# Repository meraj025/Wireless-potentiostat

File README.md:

# Wireless configurable potentiostat
Using Redbear Nano V2 and LMP91000 (TI) a wireless configurable and acquisition interface is designed, developed and tested.
Repository Contents
-------------------
* **/Libraries** - Arduino library and example sketches.
* **/PCB** - All Eagle design files (.brd, .sch)
* **/python** - All python files and GUI (.py, .ui)

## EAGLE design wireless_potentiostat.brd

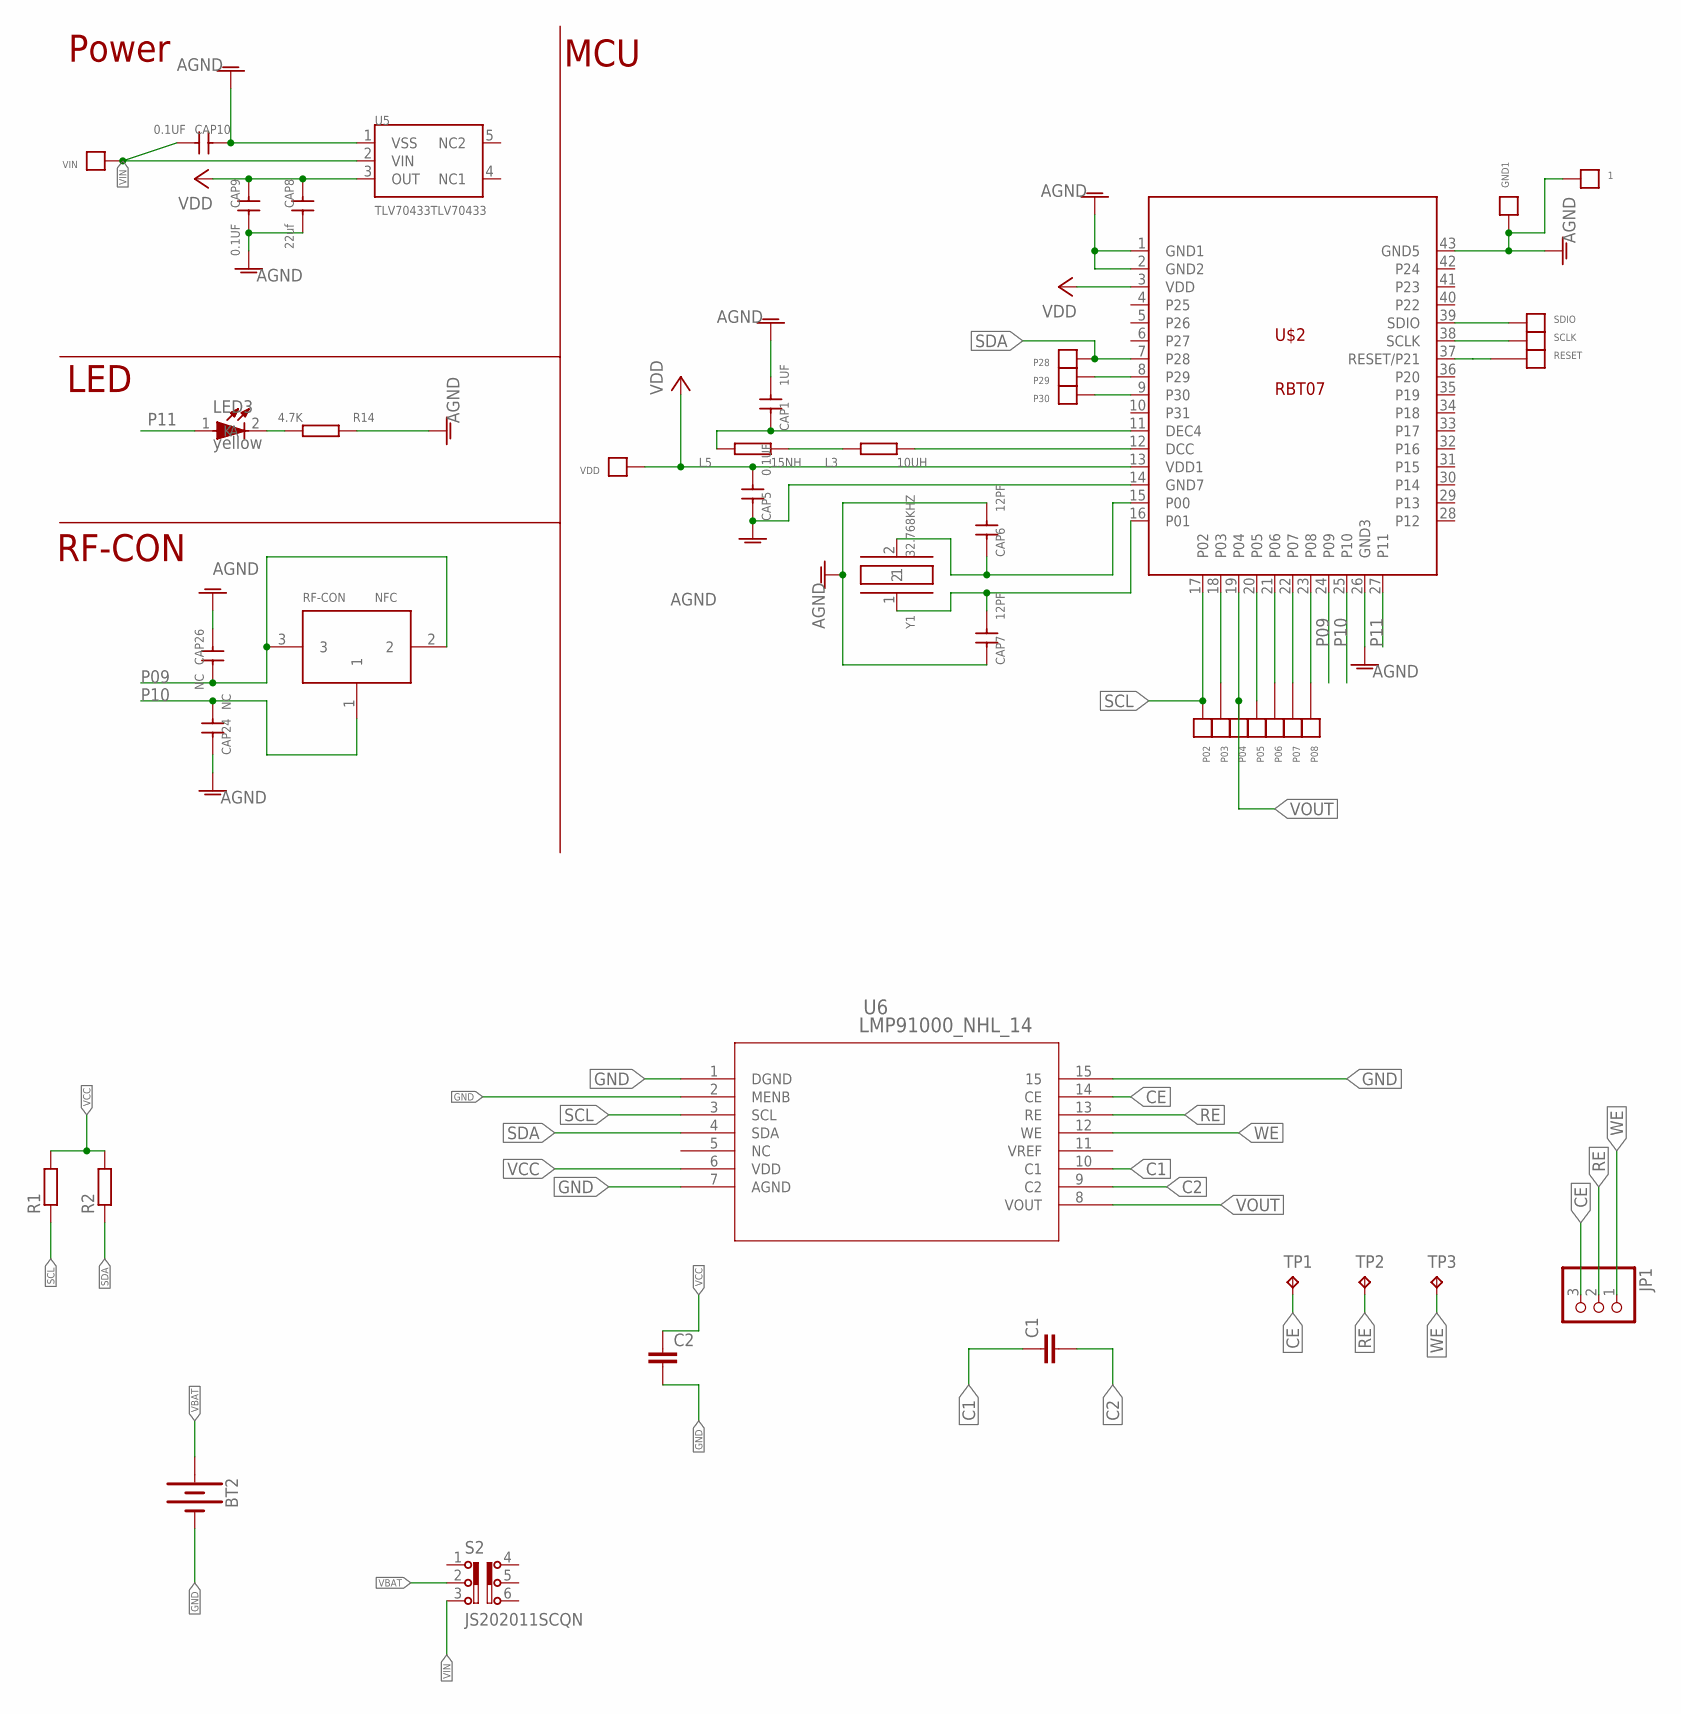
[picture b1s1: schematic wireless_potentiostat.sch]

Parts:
1: TPDOT_1; DOT_1
BT2: BATTERY-24.5MM_PTH; BATTCON_24.5MM_PTH
C1, C2: C-EUC0603; C0603
CAP1: 1UF; C-0402
CAP5, CAP9, CAP10: 0.1UF; C-0402
CAP6, CAP7: 12PF; C-0402
CAP8: 22uf; C0805
CAP24, CAP26: NC; C-0402
GND1: TPDOT_1.5; DOT_1.5
JP1: PINHD-1X3; 1X03
L3: 10UH; R0603
L5: 15NH; R0402
LED3: yellow; LED0603
P02, P04, P05, P29, P30: TPDOT_1.5; DOT_1.5
P03, P06, P07, P08: 1P
P28: TPTPEB; TPEB
R1, R2: R-EU_R0603; R0603
R14: 4.7K; R0402
RESET: 1P
RF-CON: NFC; IPEX
S2: JS202011SCQN
SCLK: TPDOT_1.5; DOT_1.5
SDIO: TPDOT_1.5; DOT_1.5
TP1, TP2, TP3: TPPAD1-13; P1-13
U5: TLV70433TLV70433; SOT-23-5
U6: LMP91000_NHL_14; SDA14B
U$2: RBT07
VDD: TPTPEB; TPEB
VIN: TPDOT_1; DOT_1
Y1: 32.768KHZ; CRY_3215

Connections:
C1: C1.1, U6.10 (C1)
C2: C1.2, U6.9 (C2)
CE: JP1.3, TP1.TP, U6.14 (CE)
GND: 1.1, BT2.2 (-), C2.2, CAP1.1, CAP5.2, CAP6.1, CAP7.2, CAP8.1, CAP9.1, CAP10.2, CAP24.2, CAP26.2, GND1.1, R14.1, U5.1 (VSS), U6.1 (DGND), U6.2 (MENB), U6.7 (AGND), U6.15, U$2.1 (GND1), U$2.2 (GND2), U$2.14 (GND7), U$2.26 (GND3), U$2.43 (GND5)
unnamed: L3.1, L5.2
unnamed: CAP1.2, L5.1, U$2.11 (DEC4)
unnamed: L3.2, U$2.12 (DCC)
unnamed: SDIO.1, U$2.39 (SDIO)
unnamed: SCLK.1, U$2.38 (SCLK)
unnamed: RESET.P$1, U$2.37 (RESET/P21)
unnamed: CAP7.1, U$2.16 (P01), Y1.1
unnamed: CAP6.2, U$2.15 (P00), Y1.2
unnamed: P03.P$1, U$2.18 (P03)
unnamed: P05.1, U$2.20 (P05)
unnamed: P06.P$1, U$2.21 (P06)
unnamed: P29.1, U$2.8 (P29)
unnamed: P07.P$1, U$2.22 (P07)
unnamed: P08.P$1, U$2.23 (P08)
unnamed: LED3.2 (K), R14.2
unnamed: P30.1, U$2.9 (P30)
P09: CAP26.1, RF-CON.2, RF-CON.3, U$2.24 (P09)
P10: CAP24.1, RF-CON.1, U$2.25 (P10)
P11: LED3.1 (A), U$2.27 (P11)
RE: JP1.2, TP2.TP, U6.13 (RE)
SCL: P02.1, R1.1, U6.3 (SCL), U$2.17 (P02)
SDA: P28.1, R2.1, U6.4 (SDA), U$2.7 (P28)
VBAT: BT2.3 (+), S2.2
VCC: C2.1, CAP5.1, CAP8.2, CAP9.2, R1.2, R2.2, U5.3 (OUT), U6.6 (VDD), U$2.3 (VDD), U$2.13 (VDD1), VDD.1
VIN: CAP10.1, S2.3, U5.2 (VIN), VIN.1
VOUT: P04.1, U6.8 (VOUT), U$2.19 (P04)
WE: JP1.1, TP3.TP, U6.12 (WE)

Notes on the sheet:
LED
RF-CON
Power
MCU

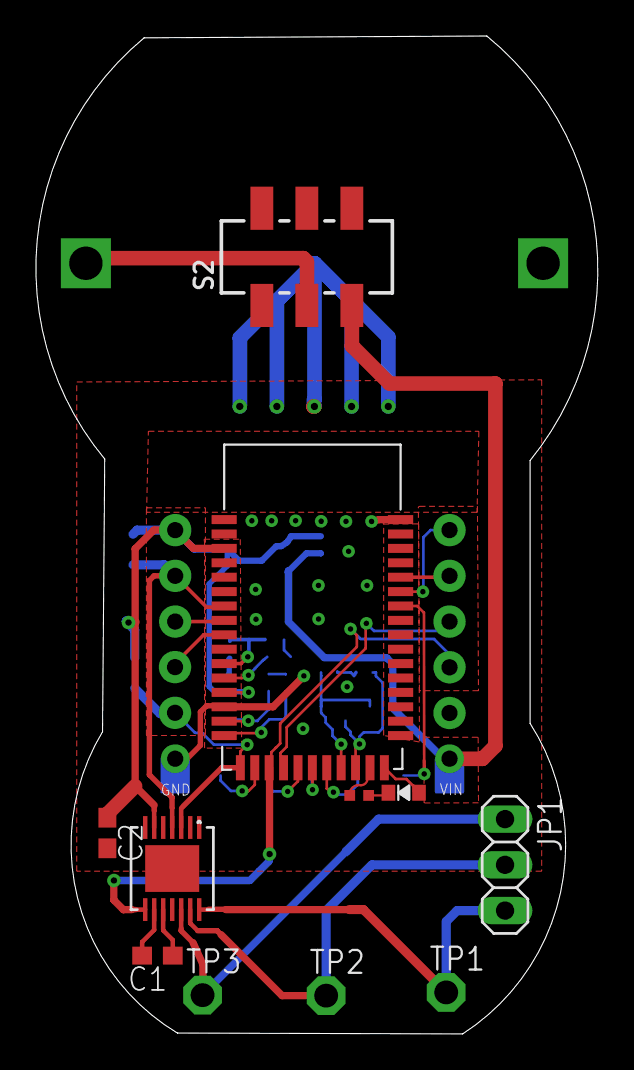
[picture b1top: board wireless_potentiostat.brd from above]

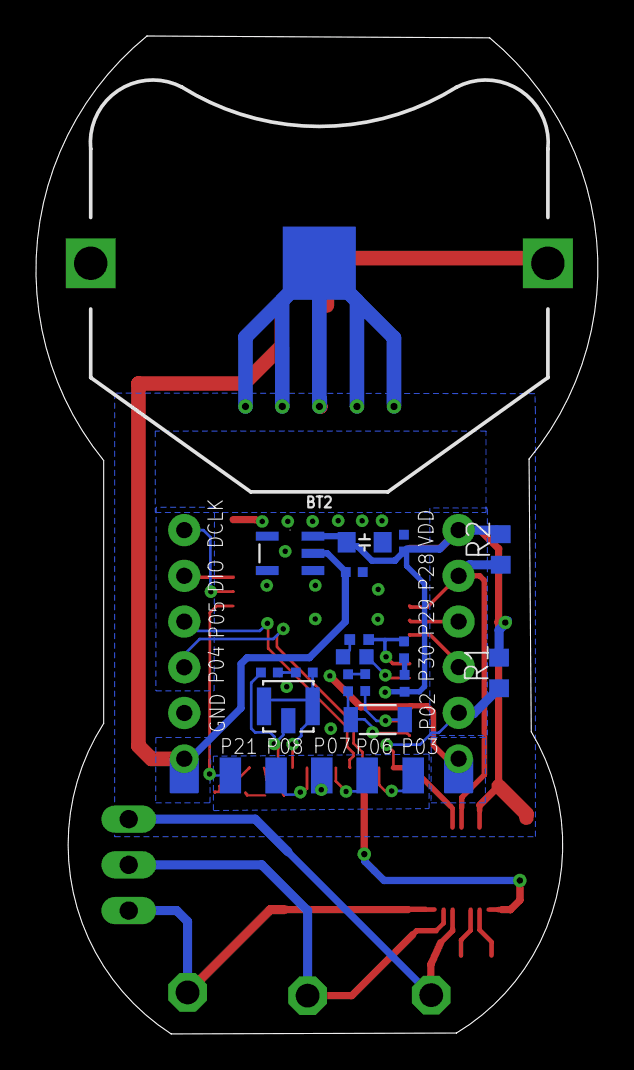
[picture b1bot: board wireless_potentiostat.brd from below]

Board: 2 copper layers, 31.2 x 55.4 mm, 45 parts (23 on the bottom side), 31 nets.

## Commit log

2020-01-30 Hardware/

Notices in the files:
parts and their libraries:
SparkFun-Batteries: Licensing: Creative Commons ShareAlike 4.0 International - https://creativecommons.org/licenses/by-sa/4.0
switch-ck: Copyright (C) 2011, Bob Starr
